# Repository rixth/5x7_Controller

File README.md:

# 5x7 Controller

This is a project that provides hardware & firmware for a small (43x70mm) board that contains four 5x7 row-anode LED matrices.

## Controller primary components

* 4 5x7 row-anode LED matrices
* 2 Texas Instruments TLC59284 sixteen-channel LED driver (constant-current sink)
* 1 CD4022B 8-output counter
* 1 74HC540 inverting buffer
* 7 IRLML5203 P-channel mosfets
* Freescale Kinetis MKL02Z32VFM4 Cortex M0+ MCU (32k flash)
* So. Many. Interfaces.

## Brief design overview

This display is drawn row-by-row. The row to be drawn is selected by the counter, which feeds it output through an inverting-buffer, then out to the P-channel mosfets. The columns are selected by the TLC59284 which are essentially shift registers that can sink considerable (configurable) current, so you can avoid having many current limiting resistors for the LEDs.

The Kinetis MCU will be responsible for drawing the display, and receiving commands from the main controller. I have exposed the MCU's i2c, SPI and UART lines to headers.

The raw inputs for the row/column selection have also been broken out to the left side of the board - 4 pins are required (shift clk, in, latch + counter clk). This can be reduced by 1 if a solder bridge is used to tie the clock of the counter to the latch of the shift register.

## Software overview

The software is still in the planning phases, but the rough plan is to use a slim RTOS like [AtomThreads](http://atomthreads.com/) to both keep the display refeshed and take input from the host controller over i2c, SPI or serial.

The MCU will have an ASCII character set preloaded - but the command set will also allow the host to toggle single LEDs, rows and columns.

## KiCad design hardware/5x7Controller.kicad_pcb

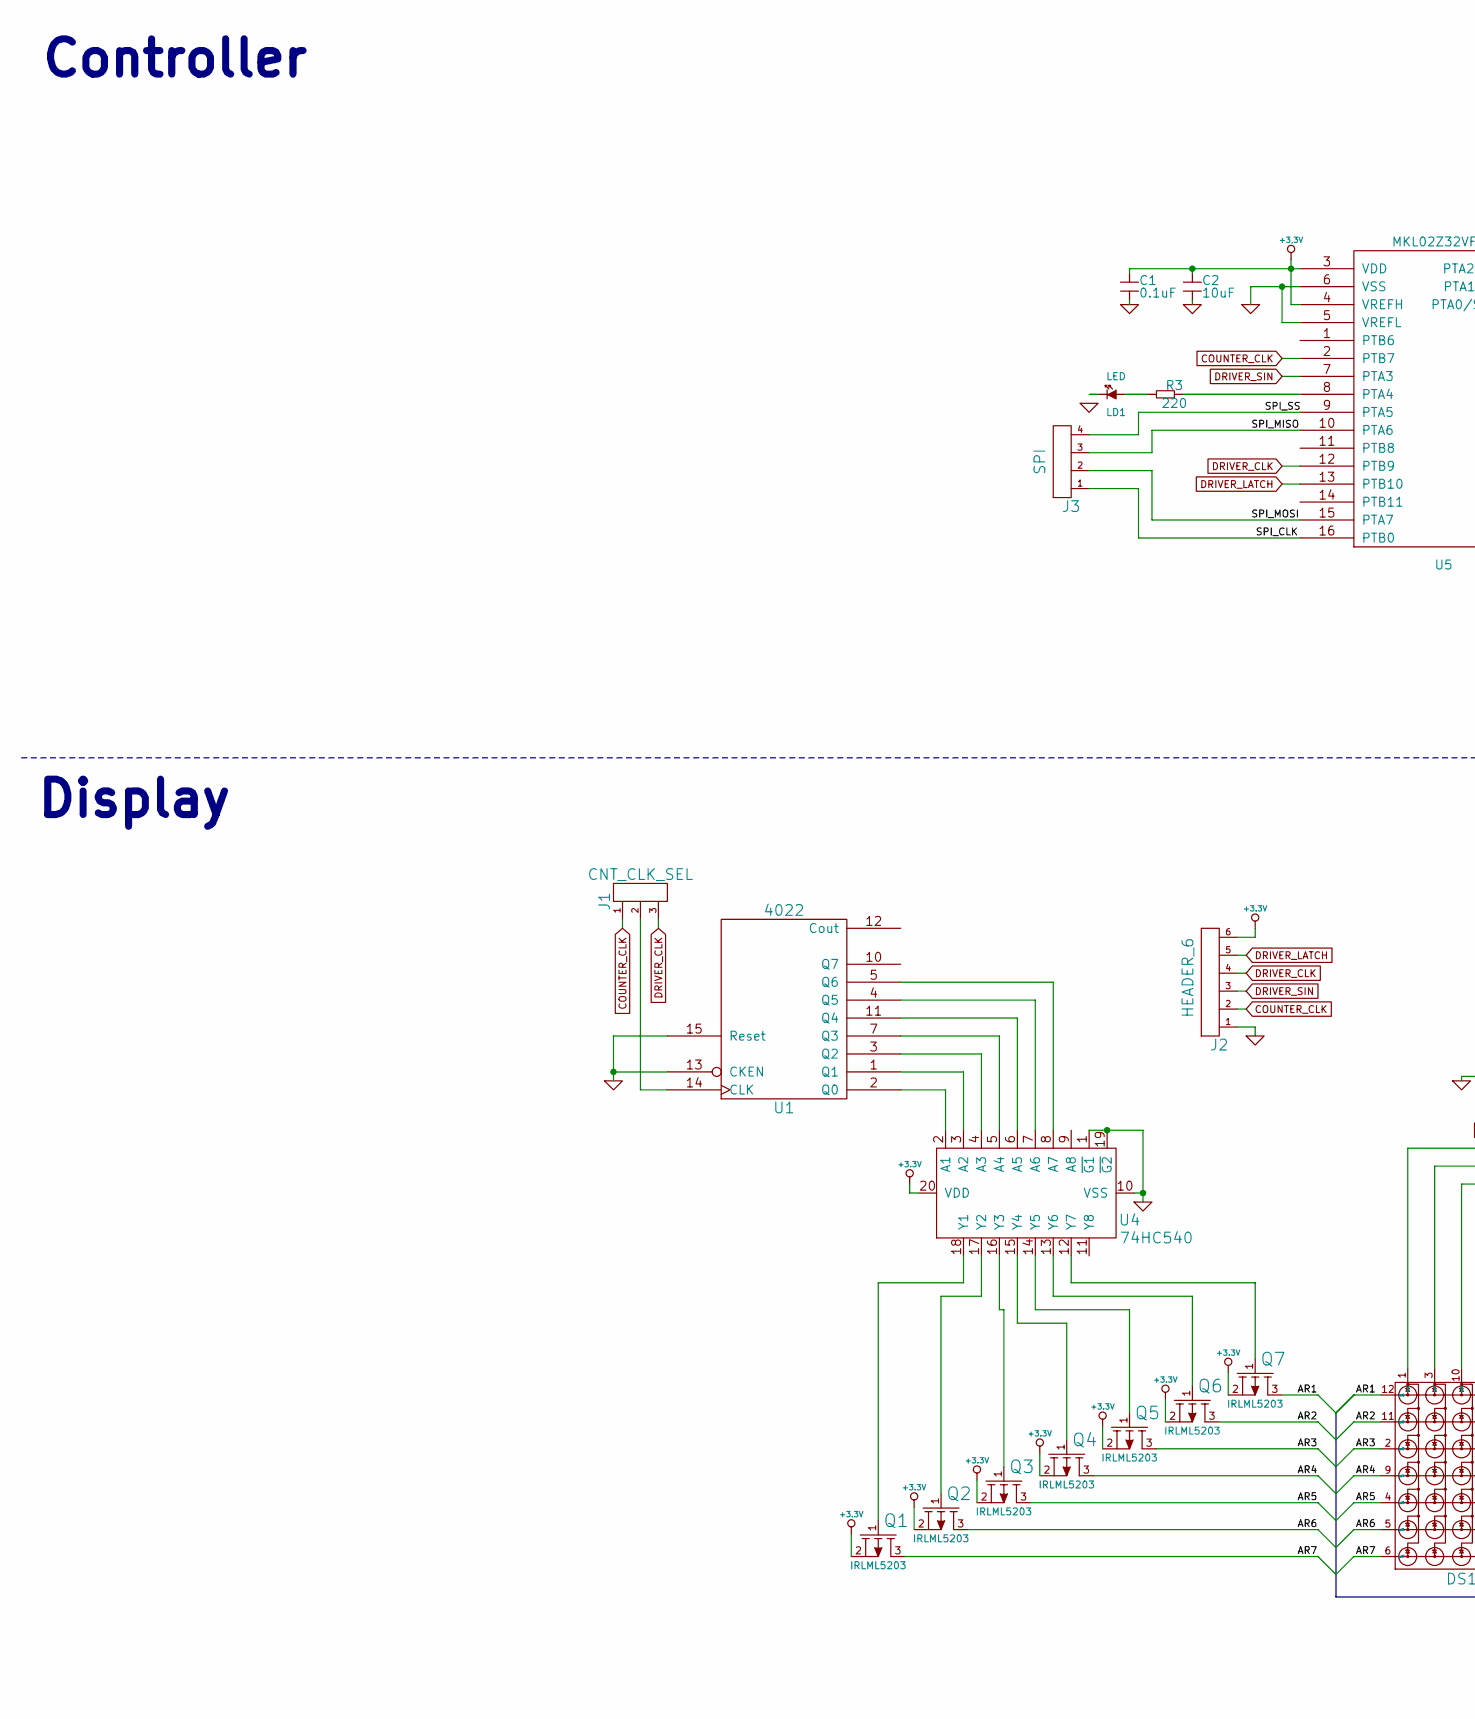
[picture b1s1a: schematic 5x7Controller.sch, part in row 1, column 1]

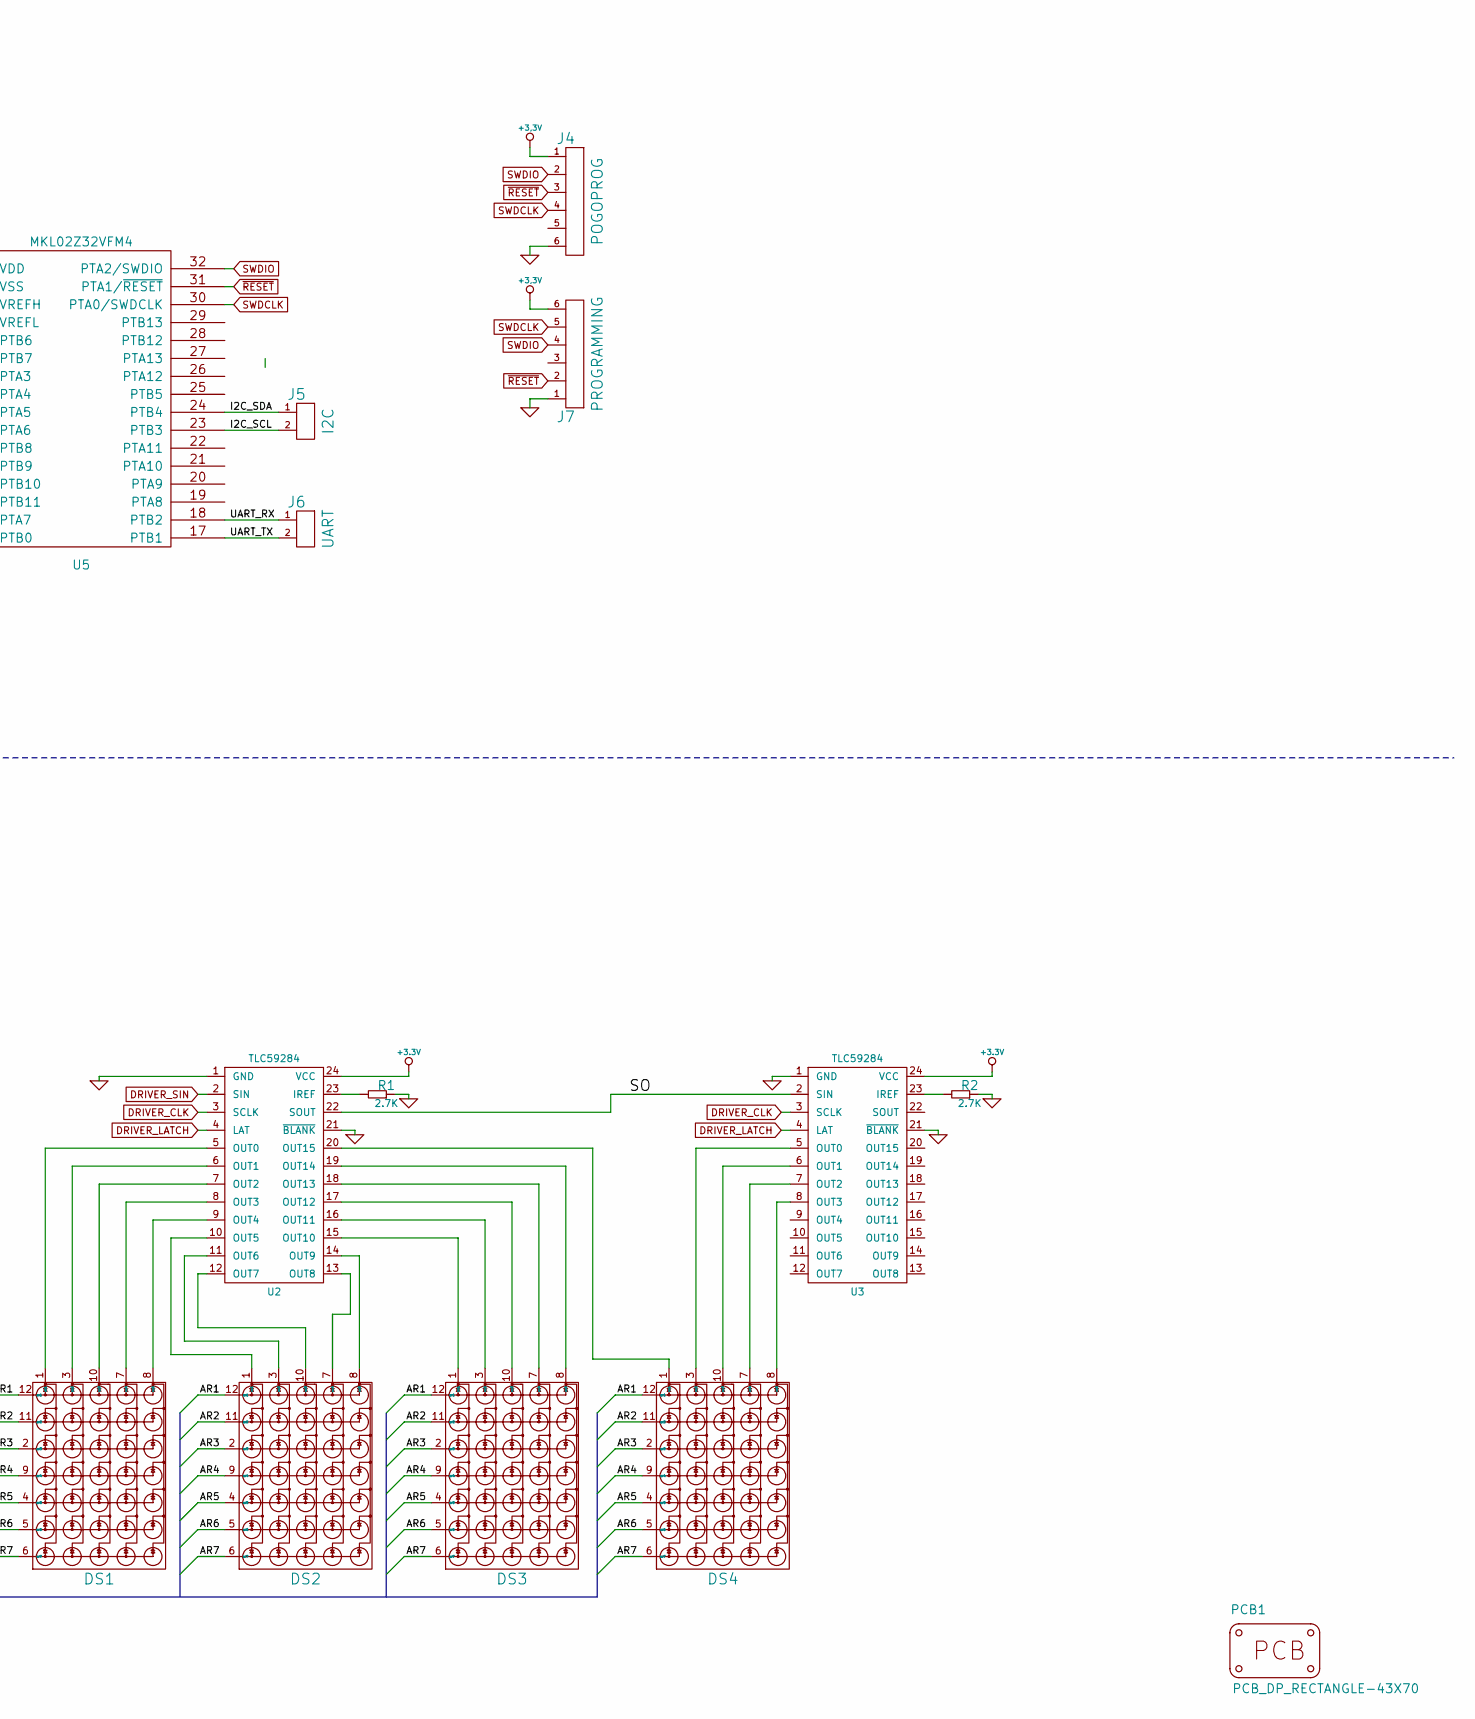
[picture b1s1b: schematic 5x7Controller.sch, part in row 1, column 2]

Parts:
C1: 0.1uF; c_0603
C2: 10uF; c_0603
DS1, DS2, DS3, DS4: VAOM-C07573G9-BW/32; VAOM-A07573G9
J1: CNT_CLK_SEL; 3-way_bridge_0603
J2: HEADER_6; pin_strip_6
J3: SPI; pin_socket_4
J4: POGOPROG; POGOPROG-CONN-OH-SMALLERVIAS
J5: I2C; pin_socket_2
J6: UART; pin_socket_2
J7: PROGRAMMING; pin_strip_6
LD1: LED; Led_0603
PCB1: PCB_DP_RECTANGLE-43X70; dp_devices-DP7043_V1
Q1, Q2, Q3, Q4, Q5, Q6, Q7: IRLML5203; sot23
R1, R2: 2.7K; r_0603
R3: 220; r_0603
U1: 4022; tssop-16
U2, U3: TLC59284; ssop-24
U4: 74HC540; tssop-20
U5: MKL02Z32VFM4; QFN-32-1EP_5x5mm_Pitch0.5mm

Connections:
/AR1: DS1.12 (ar1), DS2.12 (ar1), DS3.12 (ar1), DS4.12 (ar1), Q7.3 (D)
/AR2: DS1.11 (ar2), DS2.11 (ar2), DS3.11 (ar2), DS4.11 (ar2), Q6.3 (D)
/AR3: DS1.2 (ar3), DS2.2 (ar3), DS3.2 (ar3), DS4.2 (ar3), Q5.3 (D)
/AR4: DS1.9 (ar4), DS2.9 (ar4), DS3.9 (ar4), DS4.9 (ar4), Q4.3 (D)
/AR5: DS1.4 (ar5), DS2.4 (ar5), DS3.4 (ar5), DS4.4 (ar5), Q3.3 (D)
/AR6: DS1.5 (ar6), DS2.5 (ar6), DS3.5 (ar6), DS4.5 (ar6), Q2.3 (D)
/AR7: DS1.6 (ar7), DS2.6 (ar7), DS3.6 (ar7), DS4.6 (ar7), Q1.3 (D)
/I2C_SCL: J5.2, U5.23 (PTB3)
/I2C_SDA: J5.1, U5.24 (PTB4)
/SO: U2.22 (SOUT), U3.2 (SIN)
/SPI_CLK: J3.1, U5.16 (PTB0)
/SPI_MISO: J3.3, U5.10 (PTA6)
/SPI_MOSI: J3.2, U5.15 (PTA7)
/SPI_SS: J3.4, U5.9 (PTA5)
/UART_RX: J6.1, U5.18 (PTB2)
/UART_TX: J6.2, U5.17 (PTB1)
COUNTER_CLK: J1.1, J2.2, U5.2 (PTB7)
DRIVER_CLK: J1.3, J2.4, U2.3 (SCLK), U3.3 (SCLK), U5.12 (PTB9)
DRIVER_LATCH: J2.5, U2.4 (LAT), U3.4 (LAT), U5.13 (PTB10)
DRIVER_SIN: J2.3, U2.2 (SIN), U5.7 (PTA3)
GND: C1.2, C2.2, J2.1, J4.6, J7.1, R1.1, R2.1, U1.13 (CKEN), U1.15 (Reset), U2.1 (GND), U2.21 (~BLANK), U3.1 (GND), U3.21 (~BLANK), U4.1 (~G1), U4.10 (VSS), U4.19 (~G2), U5.5 (VREFL), U5.6 (VSS)
unnamed: DS1.1 (cc1), U2.5 (OUT0)
unnamed: DS1.3 (cc2), U2.6 (OUT1)
unnamed: DS1.7 (cc4), U2.8 (OUT3)
unnamed: DS1.8 (cc5), U2.9 (OUT4)
unnamed: DS1.10 (cc3), U2.7 (OUT2)
unnamed: DS2.1 (cc1), U2.10 (OUT5)
unnamed: DS2.3 (cc2), U2.11 (OUT6)
unnamed: DS2.7 (cc4), U2.13 (OUT8)
unnamed: DS2.8 (cc5), U2.14 (OUT9)
unnamed: DS2.10 (cc3), U2.12 (OUT7)
unnamed: DS3.1 (cc1), U2.15 (OUT10)
unnamed: DS3.3 (cc2), U2.16 (OUT11)
unnamed: DS3.7 (cc4), U2.18 (OUT13)
unnamed: DS3.8 (cc5), U2.19 (OUT14)
unnamed: DS3.10 (cc3), U2.17 (OUT12)
unnamed: DS4.1 (cc1), U2.20 (OUT15)
unnamed: DS4.3 (cc2), U3.5 (OUT0)
unnamed: DS4.7 (cc4), U3.7 (OUT2)
unnamed: DS4.8 (cc5), U3.8 (OUT3)
unnamed: DS4.10 (cc3), U3.6 (OUT1)
unnamed: J1.2, U1.14 (CLK)
unnamed: LD1.1 (A), R3.2
unnamed: Q1.1 (G), U4.18 (Y1)
unnamed: Q2.1 (G), U4.17 (Y2)
unnamed: Q3.1 (G), U4.16 (Y3)
unnamed: Q4.1 (G), U4.15 (Y4)
unnamed: Q5.1 (G), U4.14 (Y5)
unnamed: Q6.1 (G), U4.13 (Y6)
unnamed: Q7.1 (G), U4.12 (Y7)
unnamed: R1.2, U2.23 (IREF)
unnamed: R2.2, U3.23 (IREF)
unnamed: R3.1, U5.8 (PTA4)
unnamed: U1.1 (Q1), U4.3 (A2)
unnamed: U1.2 (Q0), U4.2 (A1)
unnamed: U1.3 (Q2), U4.4 (A3)
unnamed: U1.4 (Q5), U4.7 (A6)
unnamed: U1.5 (Q6), U4.8 (A7)
unnamed: U1.7 (Q3), U4.5 (A4)
unnamed: U1.11 (Q4), U4.6 (A5)
SWDCLK: J4.4, J7.5, U5.30 (PTA0/SWDCLK)
SWDIO: J4.2, J7.4, U5.32 (PTA2/SWDIO)
~RESET: J4.3, J7.2, U5.31 (PTA1/~RESET)

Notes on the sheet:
Display
Controller

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
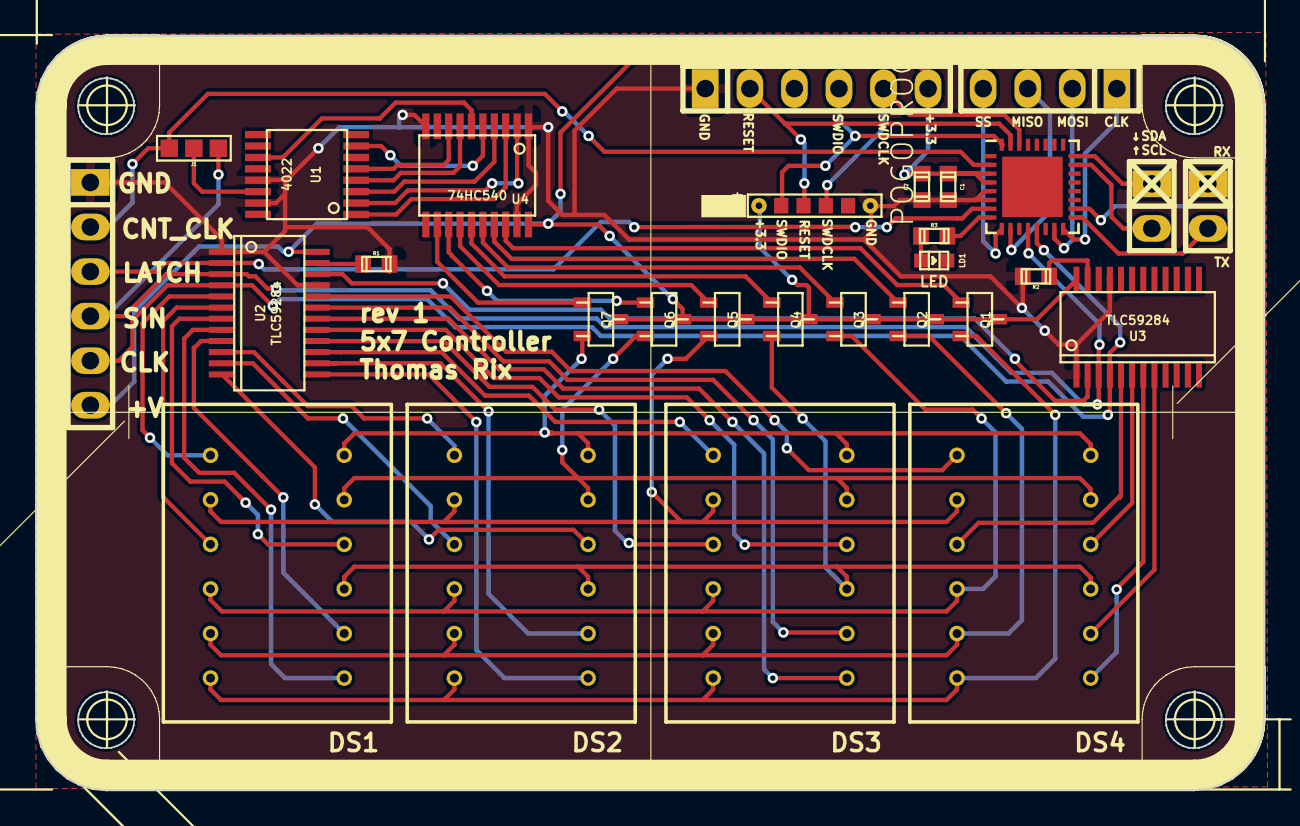
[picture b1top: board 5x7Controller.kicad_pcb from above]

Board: 2 copper layers, 70.0 x 43.0 mm, 30 parts (0 on the bottom side), 64 nets.

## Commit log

2015-08-06 Move outputs, add svg and pdfs
